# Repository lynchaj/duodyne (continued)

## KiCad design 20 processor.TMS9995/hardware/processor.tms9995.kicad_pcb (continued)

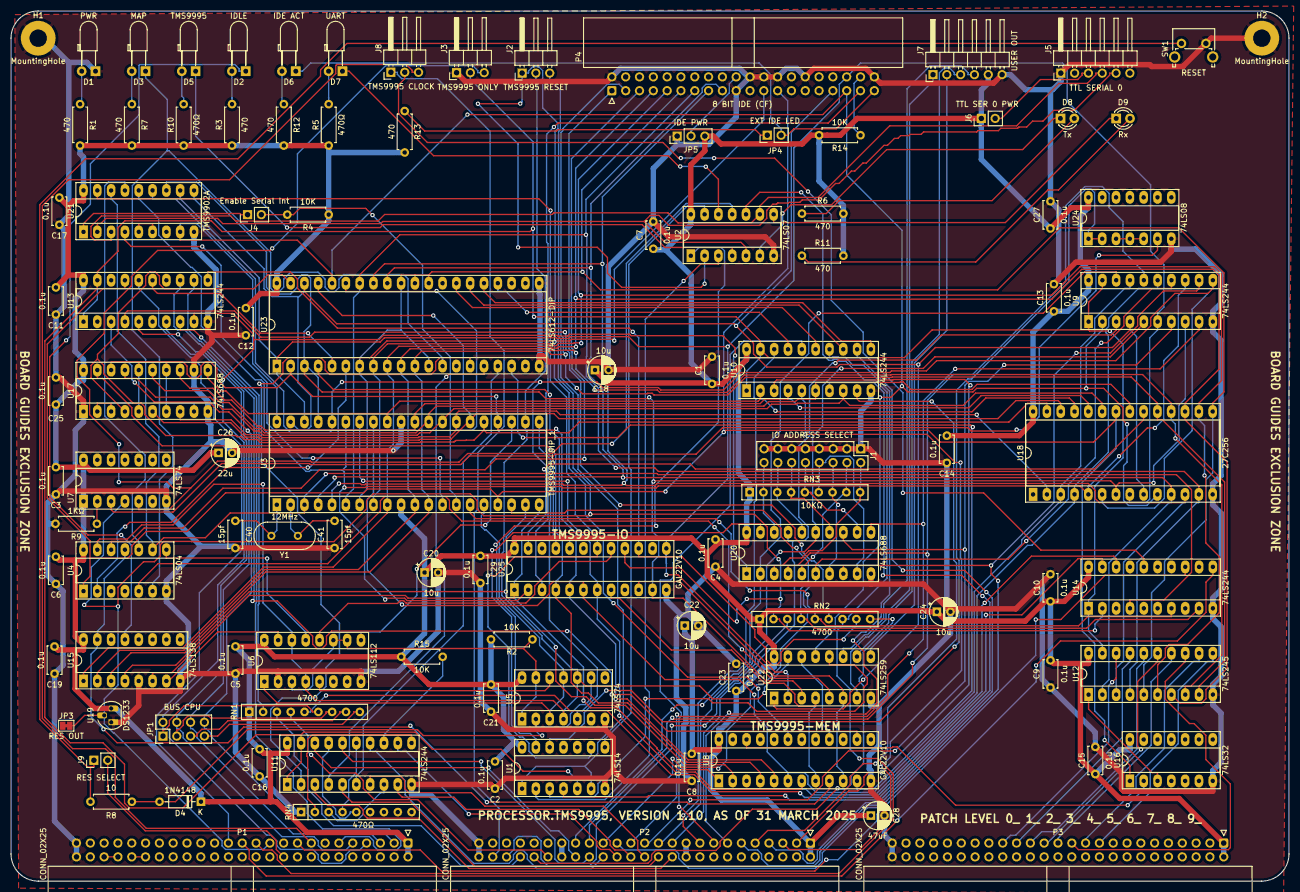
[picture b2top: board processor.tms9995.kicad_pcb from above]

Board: 2 copper layers, 235.0 x 160.0 mm, 105 parts (0 on the bottom side), 187 nets.

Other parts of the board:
R9: 1KΩ; R_Axial_DIN0207_L6.3mm_D2.5mm_P7.62mm_Horizontal

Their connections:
GND: R9.2; also elsewhere on the board
unnamed 203: R9.1; also elsewhere on the board

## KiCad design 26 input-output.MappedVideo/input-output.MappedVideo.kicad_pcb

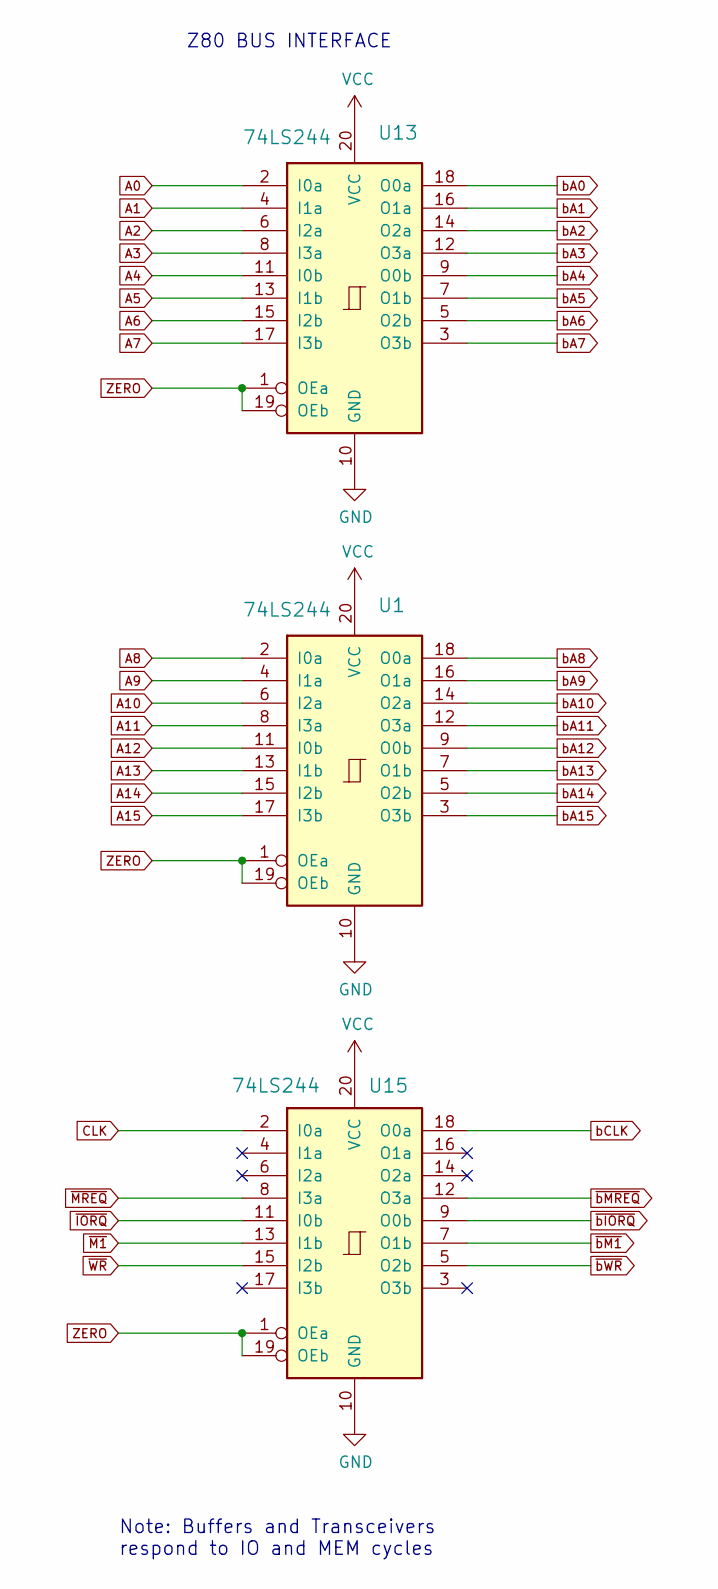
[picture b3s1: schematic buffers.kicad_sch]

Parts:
U1, U13, U15: 74LS244; DIP-20_W7.62mm

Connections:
A0: U13.2 (I0a); also elsewhere on the board
A1: U13.4 (I1a); also elsewhere on the board
A2: U13.6 (I2a); also elsewhere on the board
A3: U13.8 (I3a); also elsewhere on the board
A4: U13.11 (I0b); also elsewhere on the board
A5: U13.13 (I1b); also elsewhere on the board
A6: U13.15 (I2b); also elsewhere on the board
A7: U13.17 (I3b); also elsewhere on the board
A8: U1.2 (I0a); also elsewhere on the board
A9: U1.4 (I1a); also elsewhere on the board
A10: U1.6 (I2a); also elsewhere on the board
A11: U1.8 (I3a); also elsewhere on the board
A12: U1.11 (I0b); also elsewhere on the board
A13: U1.13 (I1b); also elsewhere on the board
A14: U1.15 (I2b); also elsewhere on the board
A15: U1.17 (I3b); also elsewhere on the board
CLK: U15.2 (I0a); also elsewhere on the board
GND: U1.10 (GND), U13.10 (GND), U15.10 (GND); also elsewhere on the board
VCC: U1.20 (VCC), U13.20 (VCC), U15.20 (VCC); also elsewhere on the board
ZERO: U1.1 (OEa), U1.19 (OEb), U13.1 (OEa), U13.19 (OEb), U15.1 (OEa), U15.19 (OEb); also elsewhere on the board
bA0: U13.18 (O0a); also elsewhere on the board
bA1: U13.16 (O1a); also elsewhere on the board
bA2: U13.14 (O2a); also elsewhere on the board
bA3: U13.12 (O3a); also elsewhere on the board
bA4: U13.9 (O0b); also elsewhere on the board
bA5: U13.7 (O1b); also elsewhere on the board
bA6: U13.5 (O2b); also elsewhere on the board
bA7: U13.3 (O3b); also elsewhere on the board
bA8: U1.18 (O0a); also elsewhere on the board
bA9: U1.16 (O1a); also elsewhere on the board
bA10: U1.14 (O2a); also elsewhere on the board
bA11: U1.12 (O3a); also elsewhere on the board
bA12: U1.9 (O0b); also elsewhere on the board
bA13: U1.7 (O1b); also elsewhere on the board
bA14: U1.5 (O2b); also elsewhere on the board
bA15: U1.3 (O3b); also elsewhere on the board
bCLK: U15.18 (O0a); also elsewhere on the board
~IORQ: U15.11 (I0b); also elsewhere on the board
~M1: U15.13 (I1b); also elsewhere on the board
~MREQ: U15.8 (I3a); also elsewhere on the board
~WR: U15.15 (I2b); also elsewhere on the board
~bIORQ: U15.9 (O0b); also elsewhere on the board
~bM1: U15.7 (O1b); also elsewhere on the board
~bMREQ: U15.12 (O3a); also elsewhere on the board
~bWR: U15.5 (O2b); also elsewhere on the board

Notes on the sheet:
Z80 BUS INTERFACE
Note: Buffers and Transceivers respond to IO and MEM cycles

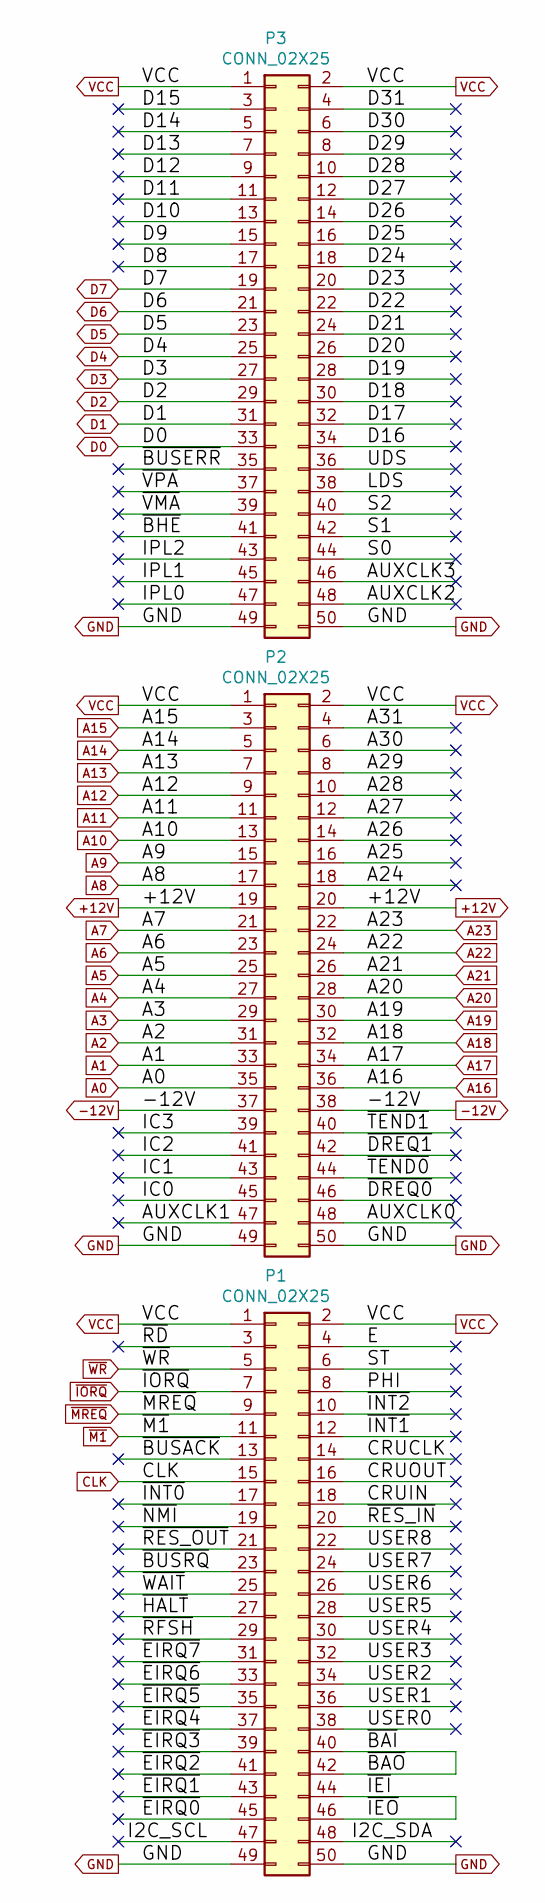
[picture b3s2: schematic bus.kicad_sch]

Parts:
P1, P2, P3: CONN_02X25; IDC-Header_2x25_P2.54mm_Horizontal

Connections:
+12V: P2.19, P2.20
-12V: P2.37, P2.38
/bus/A24: P2.18
/bus/A25: P2.16
/bus/A26: P2.14
/bus/A27: P2.12
/bus/A28: P2.10
/bus/A29: P2.8
/bus/A30: P2.6
/bus/A31: P2.4
/bus/AUXCLK0: P2.48
/bus/AUXCLK1: P2.47
/bus/AUXCLK2: P3.48
/bus/AUXCLK3: P3.46
/bus/CRUCLK: P1.14
/bus/CRUIN: P1.18
/bus/CRUOUT: P1.16
/bus/D8: P3.17
/bus/D9: P3.15
/bus/D10: P3.13
/bus/D11: P3.11
/bus/D12: P3.9
/bus/D13: P3.7
/bus/D14: P3.5
/bus/D15: P3.3
/bus/D16: P3.34
/bus/D17: P3.32
/bus/D18: P3.30
/bus/D19: P3.28
/bus/D20: P3.26
/bus/D21: P3.24
/bus/D22: P3.22
/bus/D23: P3.20
/bus/D24: P3.18
/bus/D25: P3.16
/bus/D26: P3.14
/bus/D27: P3.12
/bus/D28: P3.10
/bus/D29: P3.8
/bus/D30: P3.6
/bus/D31: P3.4
/bus/E: P1.4
/bus/I2C_SCL: P1.47
/bus/I2C_SDA: P1.48
/bus/IC0: P2.45
/bus/IC1: P2.43
/bus/IC2: P2.41
/bus/IC3: P2.39
/bus/IPL0: P3.47
/bus/IPL1: P3.45
/bus/IPL2: P3.43
/bus/LDS: P3.38
/bus/PHI: P1.8
/bus/S0: P3.44
/bus/S1: P3.42
/bus/S2: P3.40
/bus/ST: P1.6
/bus/UDS: P3.36
/bus/USER0: P1.38
/bus/USER1: P1.36
/bus/USER2: P1.34
/bus/USER3: P1.32
/bus/USER4: P1.30
/bus/USER5: P1.28
/bus/USER6: P1.26
/bus/USER7: P1.24
/bus/USER8: P1.22
/bus/~BAI: P1.40, P1.42
/bus/~BHE: P3.41
/bus/~BUSACK: P1.13
/bus/~BUSERR: P3.35
/bus/~BUSRQ: P1.23
/bus/~DREQ0: P2.46
/bus/~DREQ1: P2.42
/bus/~EIRQ0: P1.45
/bus/~EIRQ1: P1.43
/bus/~EIRQ2: P1.41
/bus/~EIRQ3: P1.39
/bus/~EIRQ4: P1.37
/bus/~EIRQ5: P1.35
/bus/~EIRQ6: P1.33
/bus/~EIRQ7: P1.31
/bus/~HALT: P1.27
/bus/~IEI: P1.44, P1.46
/bus/~INT0: P1.17
/bus/~INT1: P1.12
/bus/~INT2: P1.10
/bus/~NMI: P1.19
/bus/~RD: P1.3
/bus/~RES_IN: P1.20
/bus/~RES_OUT: P1.21
/bus/~RFSH: P1.29
/bus/~TEND0: P2.44
/bus/~TEND1: P2.40
/bus/~VMA: P3.39
/bus/~VPA: P3.37
/bus/~WAIT: P1.25
A0: P2.35; also elsewhere on the board
A1: P2.33; also elsewhere on the board
A2: P2.31; also elsewhere on the board
A3: P2.29; also elsewhere on the board
A4: P2.27; also elsewhere on the board
A5: P2.25; also elsewhere on the board
A6: P2.23; also elsewhere on the board
A7: P2.21; also elsewhere on the board
A8: P2.17; also elsewhere on the board
A9: P2.15; also elsewhere on the board
A10: P2.13; also elsewhere on the board
A11: P2.11; also elsewhere on the board
A12: P2.9; also elsewhere on the board
A13: P2.7; also elsewhere on the board
A14: P2.5; also elsewhere on the board
A15: P2.3; also elsewhere on the board
A16: P2.36; also elsewhere on the board
A17: P2.34; also elsewhere on the board
A18: P2.32; also elsewhere on the board
A19: P2.30; also elsewhere on the board
A20: P2.28; also elsewhere on the board
A21: P2.26; also elsewhere on the board
A22: P2.24; also elsewhere on the board
A23: P2.22; also elsewhere on the board
CLK: P1.15; also elsewhere on the board
D0: P3.33; also elsewhere on the board
D1: P3.31; also elsewhere on the board
D2: P3.29; also elsewhere on the board
D3: P3.27; also elsewhere on the board
D4: P3.25; also elsewhere on the board
D5: P3.23; also elsewhere on the board
D6: P3.21; also elsewhere on the board
D7: P3.19; also elsewhere on the board
GND: P1.49, P1.50, P2.49, P2.50, P3.49, P3.50; also elsewhere on the board
VCC: P1.1, P1.2, P2.1, P2.2, P3.1, P3.2; also elsewhere on the board
~IORQ: P1.7; also elsewhere on the board
~M1: P1.11; also elsewhere on the board
~MREQ: P1.9; also elsewhere on the board
~WR: P1.5; also elsewhere on the board

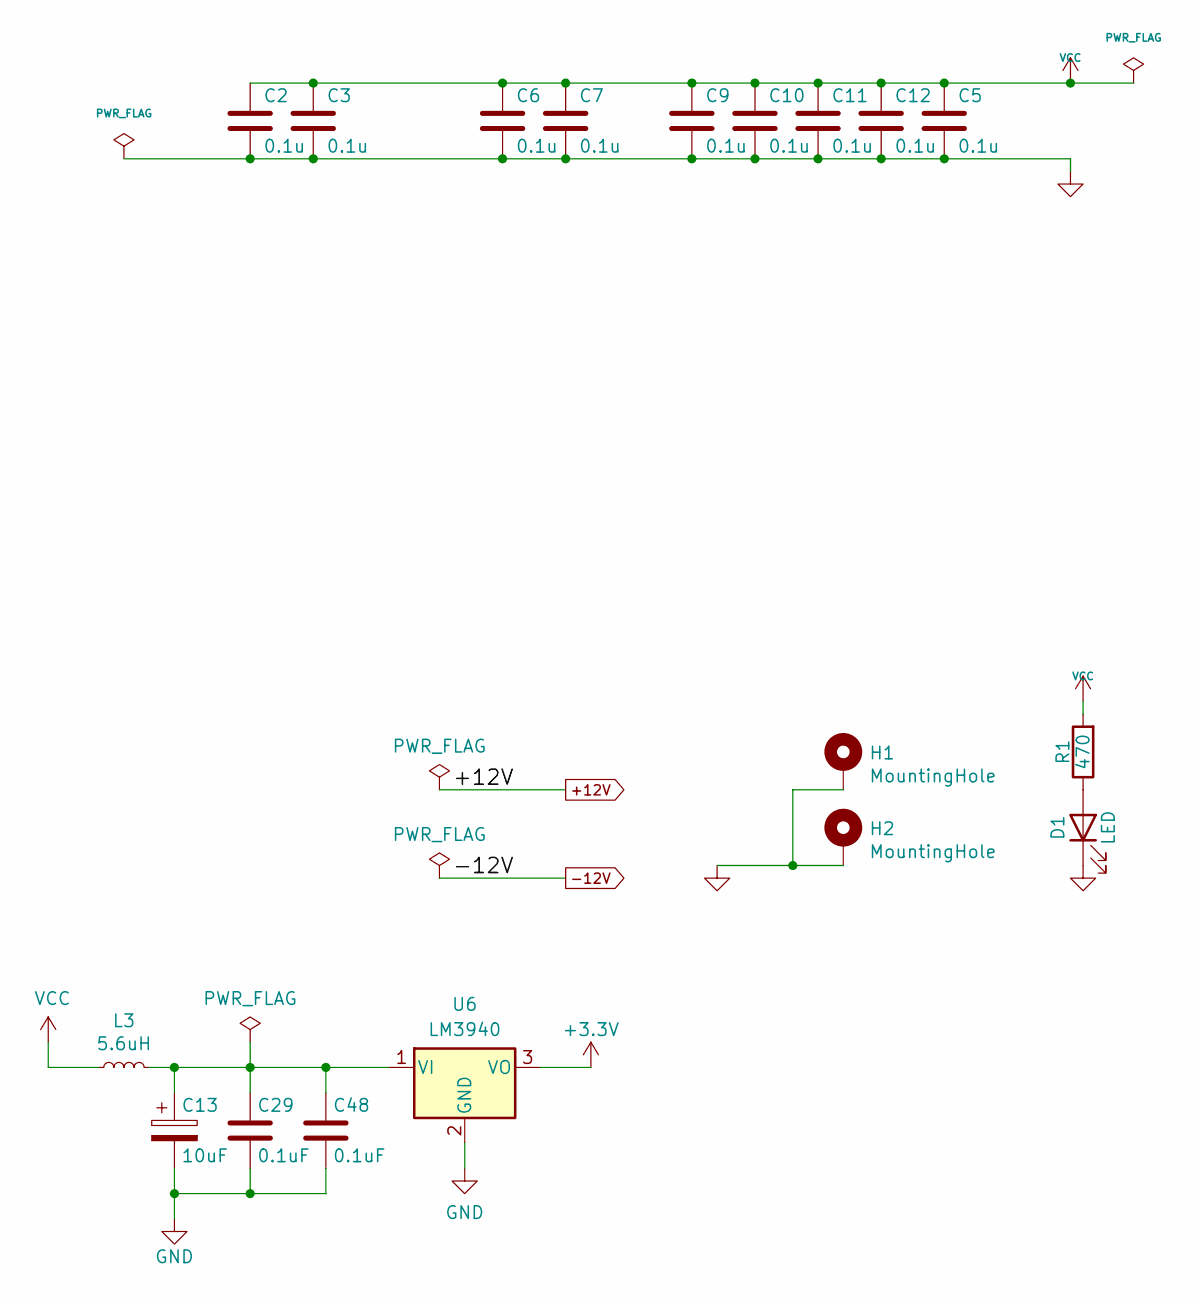
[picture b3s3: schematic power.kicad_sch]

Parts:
C2, C3, C5, C6, C7, C9, C10, C11, C12: 0.1u; C_Disc_D5.0mm_W2.5mm_P5.00mm
C13: 10uF; CP_Radial_D5.0mm_P2.50mm
C29, C48: 0.1uF; C_Disc_D5.0mm_W2.5mm_P5.00mm
D1: LED; LED_D3.0mm_Horizontal_O3.81mm_Z2.0mm
H1, H2: MountingHole; MountingHole_3.2mm_M3_Pad
L3: 5.6uH; L_Axial_L5.3mm_D2.2mm_P7.62mm_Horizontal_Vishay_IM-1
R1: 470; R_Axial_DIN0207_L6.3mm_D2.5mm_P7.62mm_Horizontal
U6: LM3940; TO-220-3_Vertical

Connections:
+3.3V: U6.3 (VO); also elsewhere on the board
GND: C2.2, C3.2, C5.2, C6.2, C7.2, C9.2, C10.2, C11.2, C12.2, C13.2, C29.2, C48.2, D1.1 (K), H1.1, H2.1, U6.2 (GND); also elsewhere on the board
unnamed: C13.1, C29.1, C48.1, L3.2, U6.1 (VI)
unnamed: D1.2 (A), R1.1
VCC: C2.1, C3.1, C5.1, C6.1, C7.1, C9.1, C10.1, C11.1, C12.1, L3.1, R1.2; also elsewhere on the board

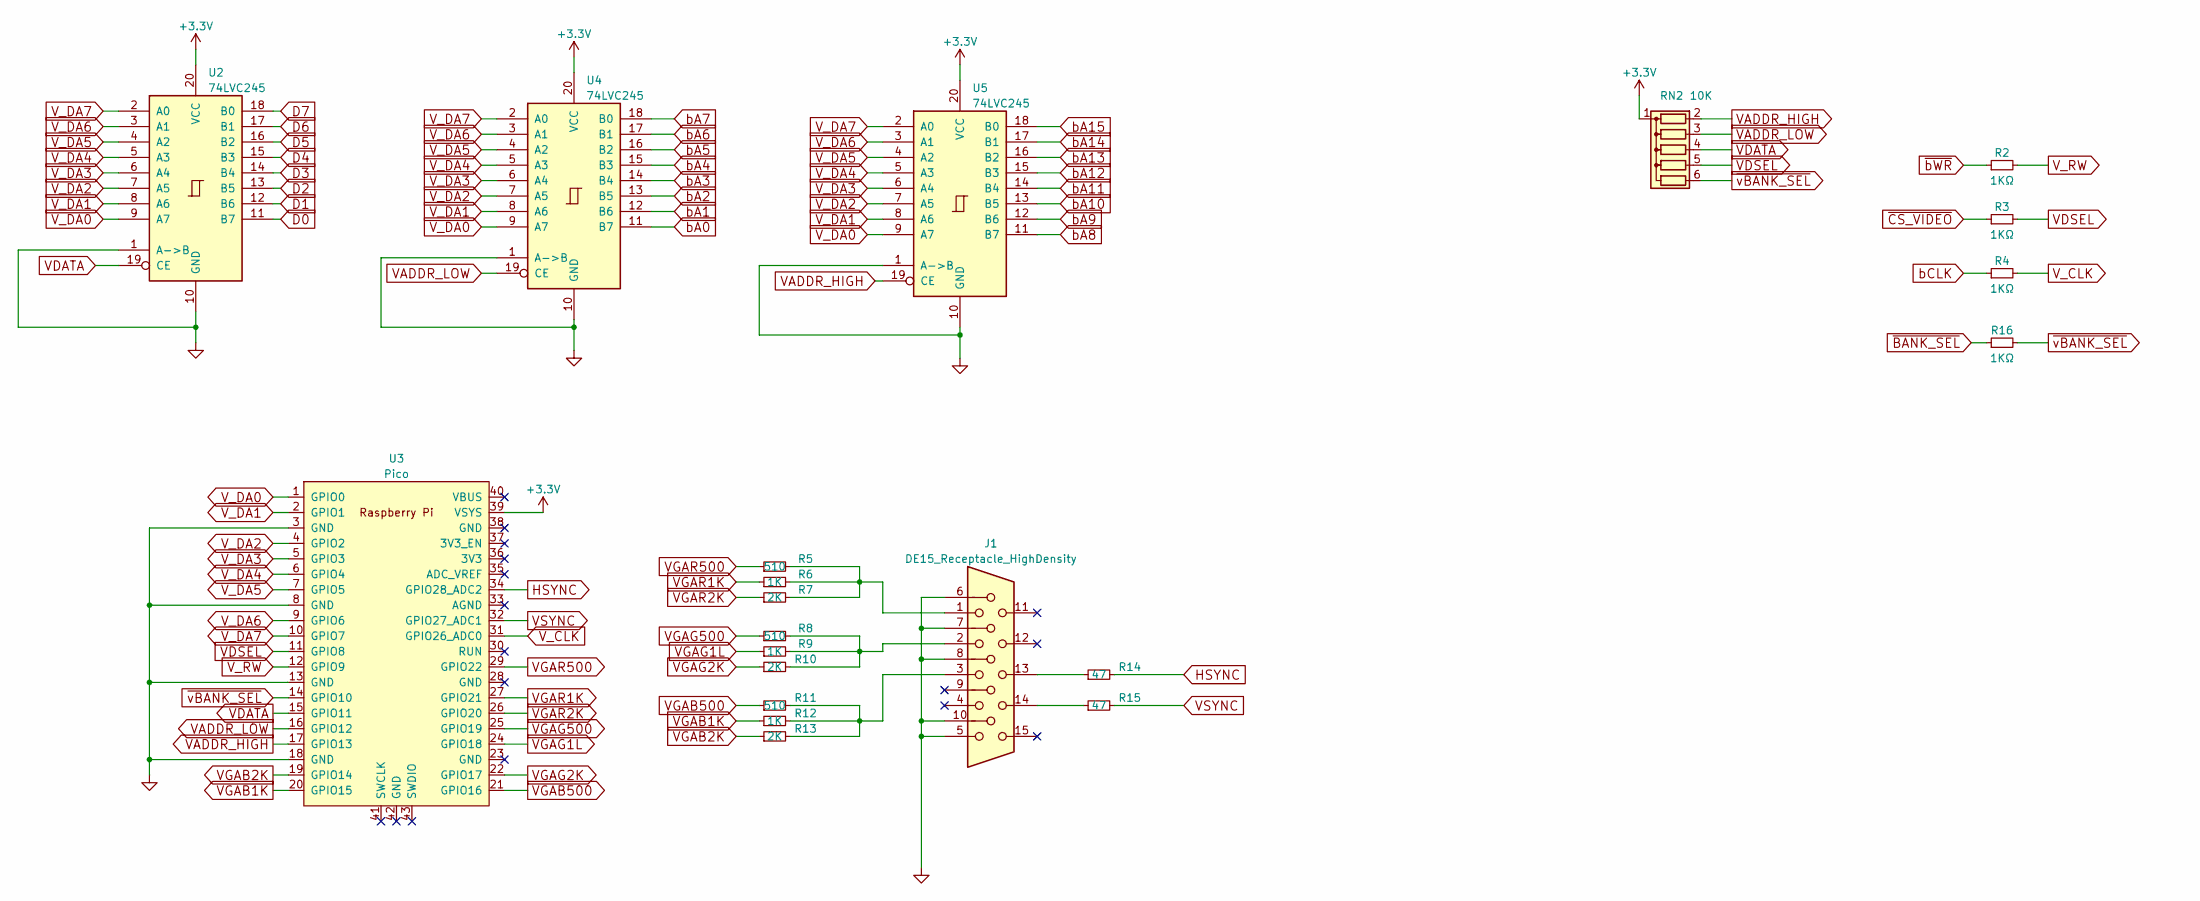
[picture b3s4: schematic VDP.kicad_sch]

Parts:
J1: DE15_Receptacle_HighDensity; DSUB-15-HD_Female_Horizontal_P2.29x1.98mm_EdgePinOffset3.03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
R2, R3, R4, R16: 1KΩ; R_Axial_DIN0204_L3.6mm_D1.6mm_P5.08mm_Horizontal
R5, R8, R11: 510; R_Axial_DIN0204_L3.6mm_D1.6mm_P5.08mm_Horizontal
R6, R9, R12: 1K; R_Axial_DIN0204_L3.6mm_D1.6mm_P5.08mm_Horizontal
R7, R10, R13: 2K; R_Axial_DIN0204_L3.6mm_D1.6mm_P5.08mm_Horizontal
R14, R15: 47; R_Axial_DIN0204_L3.6mm_D1.6mm_P5.08mm_Horizontal
RN2: 10K; R_Array_SIP6
U2, U4, U5: 74LVC245; DIP-20_W7.62mm_Socket_LongPads
U3: Pico; RPi_Pico_SMD_TH

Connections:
+3.3V: RN2.1 (common), U2.20 (VCC), U3.39 (VSYS), U4.20 (VCC), U5.20 (VCC); also elsewhere on the board
D0: U2.11 (B7); also elsewhere on the board
D1: U2.12 (B6); also elsewhere on the board
D2: U2.13 (B5); also elsewhere on the board
D3: U2.14 (B4); also elsewhere on the board
D4: U2.15 (B3); also elsewhere on the board
D5: U2.16 (B2); also elsewhere on the board
D6: U2.17 (B1); also elsewhere on the board
D7: U2.18 (B0); also elsewhere on the board
GND: J1.5, J1.6, J1.7, J1.8, J1.10, U2.1 (A->B), U2.10 (GND), U3.3 (GND), U3.8 (GND), U3.13 (GND), U3.18 (GND), U4.1 (A->B), U4.10 (GND), U5.1 (A->B), U5.10 (GND); also elsewhere on the board
HSYNC: R14.2, U3.34 (GPIO28_ADC2)
unnamed: J1.1, R5.2, R6.2, R7.2
unnamed: J1.2, R8.2, R9.2, R10.2
unnamed: J1.3, R11.2, R12.2, R13.2
unnamed: J1.13, R14.1
unnamed: J1.14, R15.1
VADDR_HIGH: RN2.2 (R1), U3.17 (GPIO13), U5.19 (CE)
VADDR_LOW: RN2.3 (R2), U3.16 (GPIO12), U4.19 (CE)
VDATA: RN2.4 (R3), U2.19 (CE), U3.15 (GPIO11)
VDSEL: R3.2, RN2.5 (R4), U3.11 (GPIO8)
VGAB1K: R12.1, U3.20 (GPIO15)
VGAB2K: R13.1, U3.19 (GPIO14)
VGAB500: R11.1, U3.21 (GPIO16)
VGAG1L: R9.1, U3.24 (GPIO18)
VGAG2K: R10.1, U3.22 (GPIO17)
VGAG500: R8.1, U3.25 (GPIO19)
VGAR1K: R6.1, U3.27 (GPIO21)
VGAR2K: R7.1, U3.26 (GPIO20)
VGAR500: R5.1, U3.29 (GPIO22)
VSYNC: R15.2, U3.32 (GPIO27_ADC1)
V_CLK: R4.2, U3.31 (GPIO26_ADC0)
V_DA0: U2.9 (A7), U3.1 (GPIO0), U4.9 (A7), U5.9 (A7)
V_DA1: U2.8 (A6), U3.2 (GPIO1), U4.8 (A6), U5.8 (A6)
V_DA2: U2.7 (A5), U3.4 (GPIO2), U4.7 (A5), U5.7 (A5)
V_DA3: U2.6 (A4), U3.5 (GPIO3), U4.6 (A4), U5.6 (A4)
V_DA4: U2.5 (A3), U3.6 (GPIO4), U4.5 (A3), U5.5 (A3)
V_DA5: U2.4 (A2), U3.7 (GPIO5), U4.4 (A2), U5.4 (A2)
V_DA6: U2.3 (A1), U3.9 (GPIO6), U4.3 (A1), U5.3 (A1)
V_DA7: U2.2 (A0), U3.10 (GPIO7), U4.2 (A0), U5.2 (A0)
V_RW: R2.2, U3.12 (GPIO9)
bA0: U4.11 (B7); also elsewhere on the board
bA1: U4.12 (B6); also elsewhere on the board
bA2: U4.13 (B5); also elsewhere on the board
bA3: U4.14 (B4); also elsewhere on the board
bA4: U4.15 (B3); also elsewhere on the board
bA5: U4.16 (B2); also elsewhere on the board
bA6: U4.17 (B1); also elsewhere on the board
bA7: U4.18 (B0); also elsewhere on the board
bA8: U5.11 (B7); also elsewhere on the board
bA9: U5.12 (B6); also elsewhere on the board
bA10: U5.13 (B5); also elsewhere on the board
bA11: U5.14 (B4); also elsewhere on the board
bA12: U5.15 (B3); also elsewhere on the board
bA13: U5.16 (B2); also elsewhere on the board
bA14: U5.17 (B1); also elsewhere on the board
bA15: U5.18 (B0); also elsewhere on the board
bCLK: R4.1; also elsewhere on the board
~BANK_SEL: R16.1; also elsewhere on the board
~CS_VIDEO: R3.1; also elsewhere on the board
~bWR: R2.1; also elsewhere on the board
~vBANK_SEL: R16.2, RN2.6 (R5), U3.14 (GPIO10)

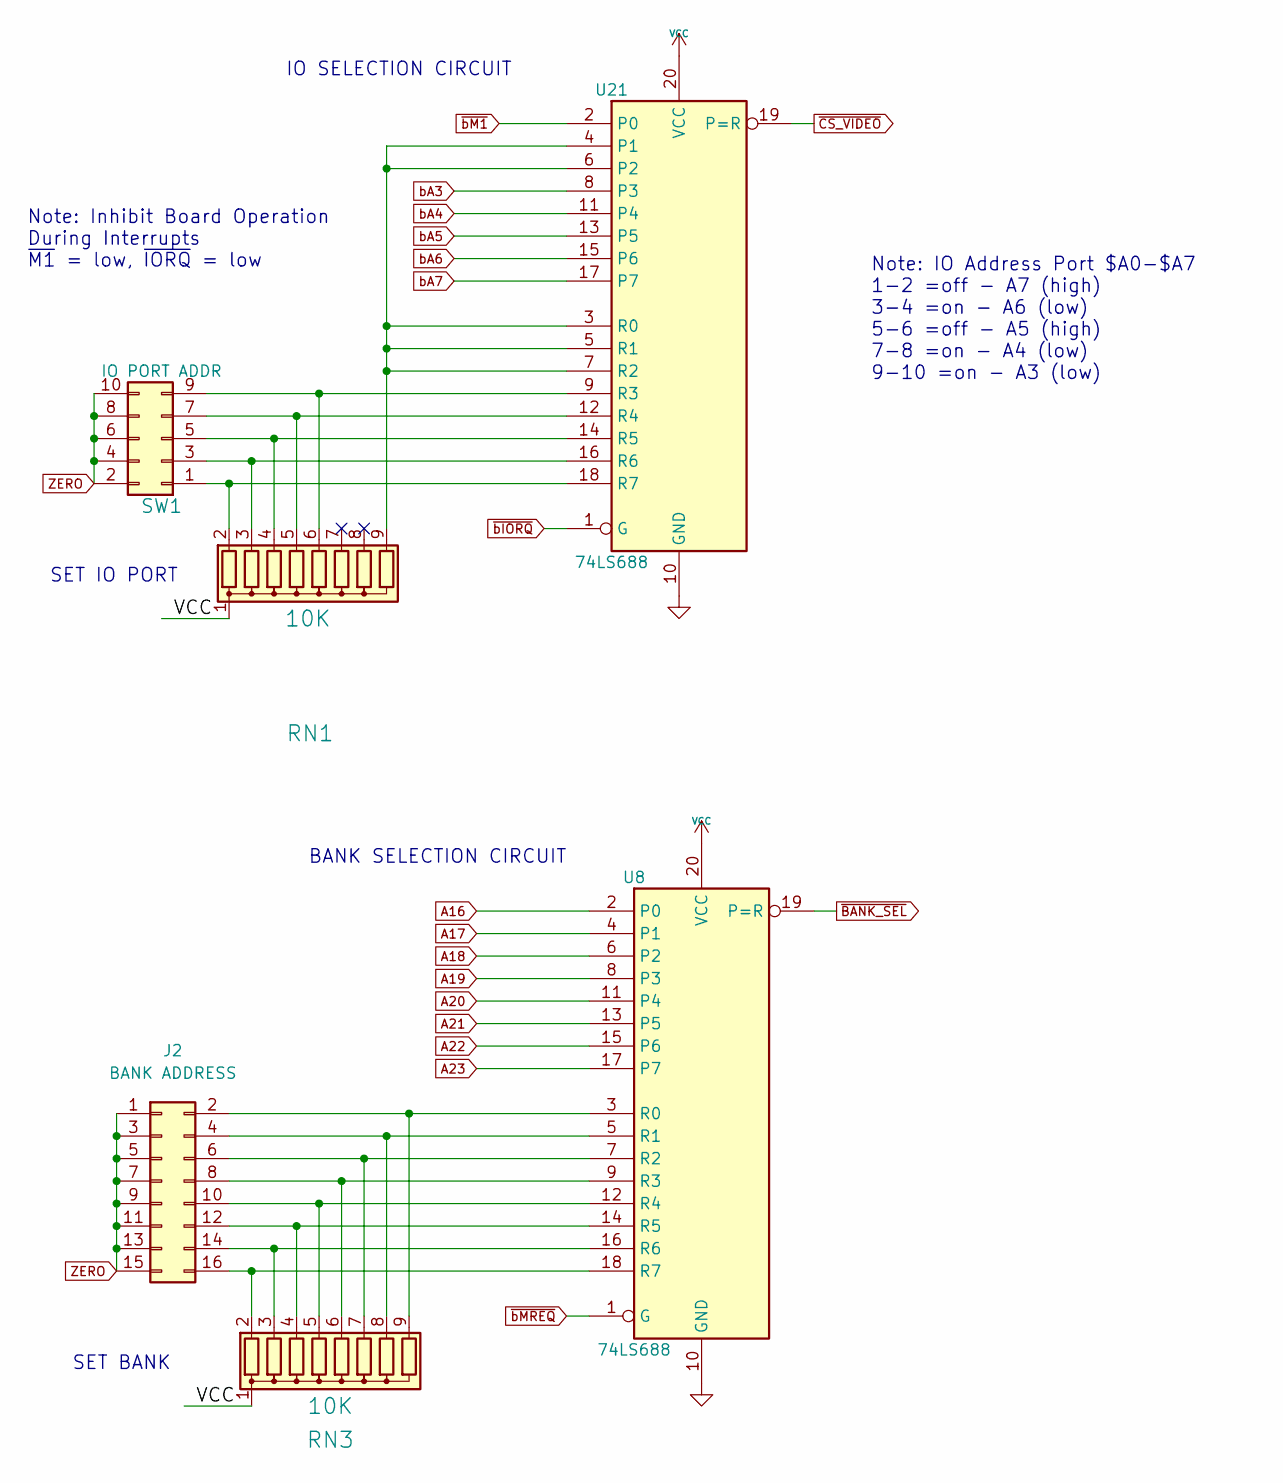
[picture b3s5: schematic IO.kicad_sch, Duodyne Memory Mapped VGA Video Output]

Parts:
J2: BANK ADDRESS; PinSocket_2x08_P2.54mm_Vertical
RN1, RN3: 10K; R_Array_SIP9
SW1: IO PORT ADDR; PinHeader_2x05_P2.54mm_Vertical
U8, U21: 74LS688; DIP-20_W7.62mm

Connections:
A16: U8.2 (P0); also elsewhere on the board
A17: U8.4 (P1); also elsewhere on the board
A18: U8.6 (P2); also elsewhere on the board
A19: U8.8 (P3); also elsewhere on the board
A20: U8.11 (P4); also elsewhere on the board
A21: U8.13 (P5); also elsewhere on the board
A22: U8.15 (P6); also elsewhere on the board
A23: U8.17 (P7); also elsewhere on the board
GND: U8.10 (GND), U21.10 (GND); also elsewhere on the board
unnamed: J2.2, RN3.9 (R8), U8.3 (R0)
unnamed: J2.4, RN3.8 (R7), U8.5 (R1)
unnamed: J2.6, RN3.7 (R6), U8.7 (R2)
unnamed: J2.8, RN3.6 (R5), U8.9 (R3)
unnamed: J2.10, RN3.5 (R4), U8.12 (R4)
unnamed: J2.12, RN3.4 (R3), U8.14 (R5)
unnamed: J2.14, RN3.3 (R2), U8.16 (R6)
unnamed: J2.16, RN3.2 (R1), U8.18 (R7)
unnamed: RN1.2 (R1), SW1.1, U21.18 (R7)
unnamed: RN1.3 (R2), SW1.3, U21.16 (R6)
unnamed: RN1.4 (R3), SW1.5, U21.14 (R5)
unnamed: RN1.5 (R4), SW1.7, U21.12 (R4)
unnamed: RN1.6 (R5), SW1.9, U21.9 (R3)
unnamed: RN1.9 (R8), U21.3 (R0), U21.4 (P1), U21.5 (R1), U21.6 (P2), U21.7 (R2)
VCC: RN1.1 (common), RN3.1 (common), U8.20 (VCC), U21.20 (VCC); also elsewhere on the board
ZERO: J2.1, J2.3, J2.5, J2.7, J2.9, J2.11, J2.13, J2.15, SW1.2, SW1.4, SW1.6, SW1.8, SW1.10; also elsewhere on the board
bA3: U21.8 (P3); also elsewhere on the board
bA4: U21.11 (P4); also elsewhere on the board
bA5: U21.13 (P5); also elsewhere on the board
bA6: U21.15 (P6); also elsewhere on the board
bA7: U21.17 (P7); also elsewhere on the board
~BANK_SEL: U8.19 (P=R); also elsewhere on the board
~CS_VIDEO: U21.19 (P=R); also elsewhere on the board
~bIORQ: U21.1 (G); also elsewhere on the board
~bM1: U21.2 (P0); also elsewhere on the board
~bMREQ: U8.1 (G); also elsewhere on the board

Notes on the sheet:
SET IO PORT
Note: IO Address Port $A0-$A7 1-2 =off - A7 (high) 3-4 =on - A6 (low) 5-6 =off - A5 (high) 7-8 =on - A4 (low) 9-10 =on - A3 (low)
SET BANK
IO SELECTION CIRCUIT
Note: Inhibit Board Operation During Interrupts ~{M1} = low, ~{IORQ} = low
BANK SELECTION CIRCUIT

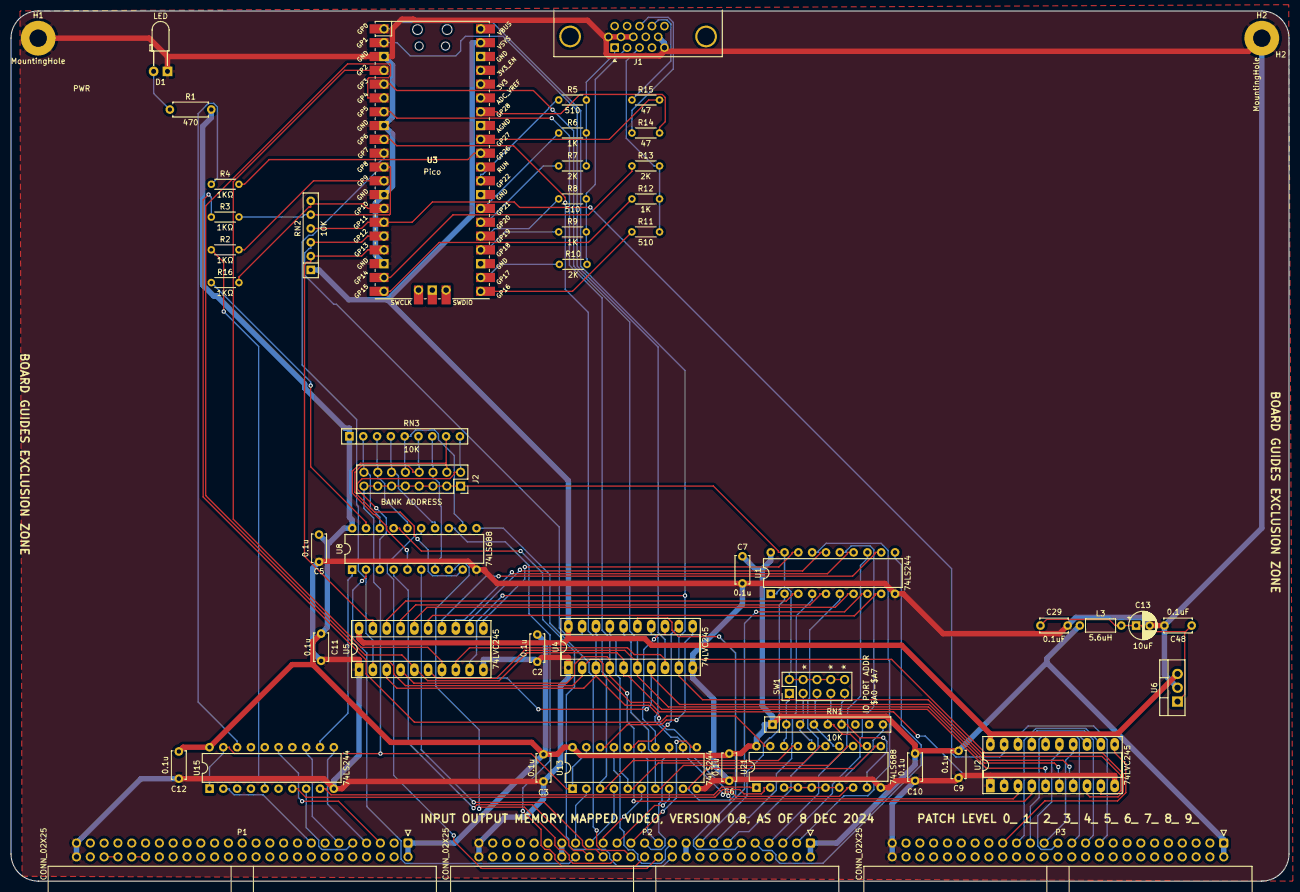
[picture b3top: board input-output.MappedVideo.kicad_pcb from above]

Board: 2 copper layers, 235.0 x 160.0 mm, 51 parts (0 on the bottom side), 115 nets.
